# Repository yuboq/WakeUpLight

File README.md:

Currently, this device turns on LED strip at 5AM, and gradually increases in brightness in a half hour period.
Demo can be found here:
https://youtu.be/3JCAbMRWAIY

Eventually, the goal for this project is to create a beautiful standalone alarm clock that can help others wake up more naturally, similar to the Philips Wake Up Light, but with more customizations

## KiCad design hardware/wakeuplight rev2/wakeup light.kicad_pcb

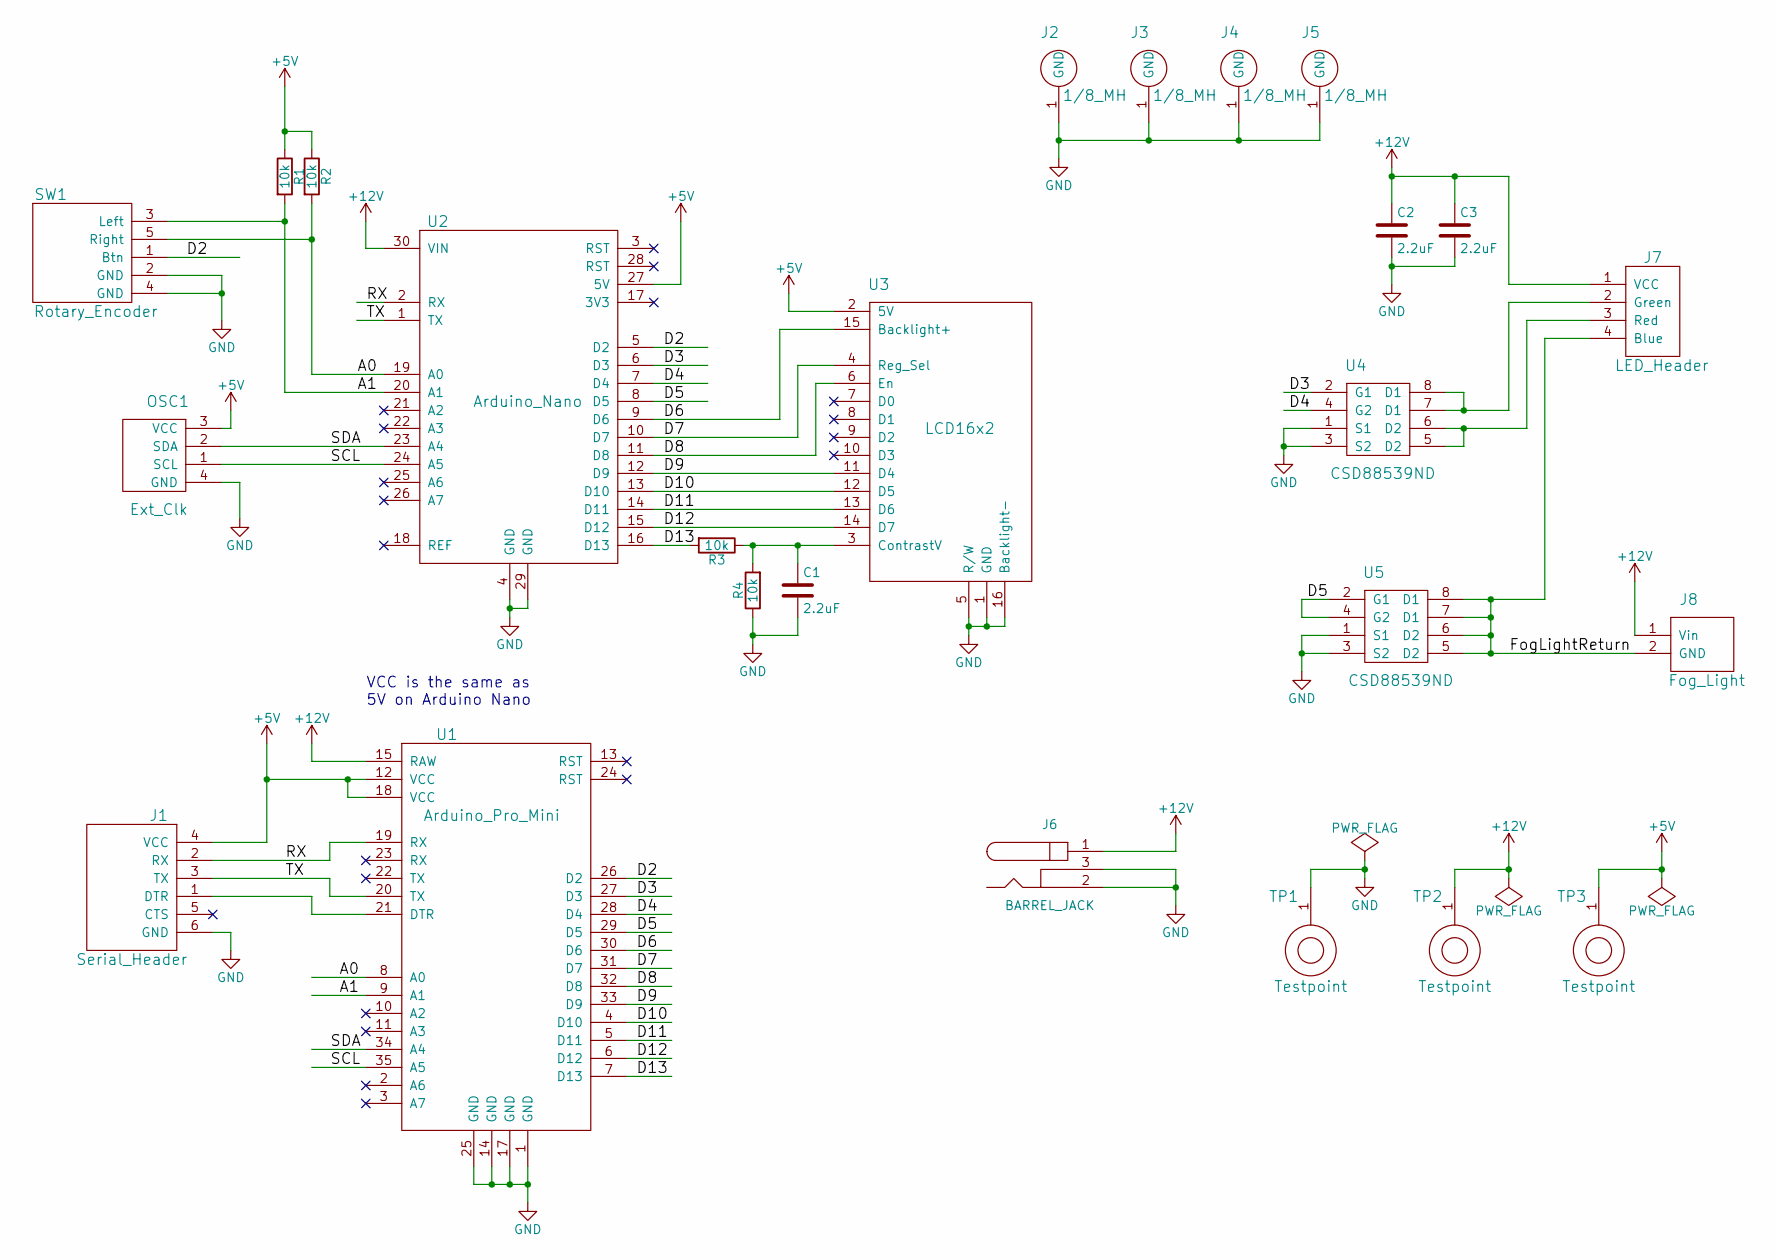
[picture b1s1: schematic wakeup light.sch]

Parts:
C1, C2, C3: 2.2uF; C_0603_HandSoldering
J1: Serial_Header; Pin_Header_Straight_1x06
J2, J3, J4, J5: 1/8_MH; 2.5mm_MH
J6: BARREL_JACK
J7: LED_Header; Pin_Header_Straight_1x04
J8: Fog_Light
OSC1: Ext_Clk; External_Clock
R1, R2, R3, R4: 10k; R_0603_HandSoldering
SW1: Rotary_Encoder; Push_Button
TP1, TP2, TP3: Testpoint
U1: Arduino_Pro_Mini
U2: Arduino_Nano
U3: LCD16x2; LCD_16x2
U4, U5: CSD88539ND; SOIC-8-N

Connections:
+5V: J1.4 (VCC), OSC1.3 (VCC), R1.1, R2.1, TP3.1, U1.12 (VCC), U1.18 (VCC), U2.27 (5V), U3.2 (5V)
+12V: C2.1, C3.1, J6.1, J7.1 (VCC), J8.1 (Vin), TP2.1, U1.15 (RAW), U2.30 (VIN)
/A0: R2.2, SW1.5 (Right), U1.8 (A0), U2.19 (A0)
/A1: R1.2, SW1.3 (Left), U1.9 (A1), U2.20 (A1)
/D2: SW1.1 (Btn), U1.26 (D2), U2.5 (D2)
/D3: U1.27 (D3), U2.6 (D3), U4.2 (G1)
/D4: U1.28 (D4), U2.7 (D4), U4.4 (G2)
/D5: U1.29 (D5), U2.8 (D5), U5.2 (G1), U5.4 (G2)
/D6: U1.30 (D6), U2.9 (D6), U3.15 (Backlight+)
/D7: U1.31 (D7), U2.10 (D7), U3.4 (Reg_Sel)
/D8: U1.32 (D8), U2.11 (D8), U3.6 (En)
/D9: U1.33 (D9), U2.12 (D9), U3.11 (D4)
/D10: U1.4 (D10), U2.13 (D10), U3.12 (D5)
/D11: U1.5 (D11), U2.14 (D11), U3.13 (D6)
/D12: U1.6 (D12), U2.15 (D12), U3.14 (D7)
/D13: R3.2, U1.7 (D13), U2.16 (D13)
/FogLightReturn: J7.4 (Blue), J8.2 (GND), U5.5 (D2), U5.6 (D2), U5.7 (D1), U5.8 (D1)
/RX: J1.2 (RX), U1.19 (RX), U2.2 (RX)
/SCL: OSC1.1 (SCL), U1.35 (A5), U2.24 (A5)
/SDA: OSC1.2 (SDA), U1.34 (A4), U2.23 (A4)
/TX: J1.3 (TX), U1.20 (TX), U2.1 (TX)
GND: C1.2, C2.2, C3.2, J1.6 (GND), J2.1, J3.1, J4.1, J5.1, J6.2, J6.3, OSC1.4 (GND), R4.1, SW1.2 (GND), SW1.4 (GND), TP1.1, U1.1 (GND), U1.14 (GND), U1.17 (GND), U1.25 (GND), U2.4 (GND), U2.29 (GND), U3.1 (GND), U3.5 (R/W), U3.16 (Backlight-), U4.1 (S1), U4.3 (S2), U5.1 (S1), U5.3 (S2)
unnamed: C1.1, R3.1, R4.2, U3.3 (ContrastV)
unnamed: J1.1 (DTR), U1.21 (DTR)
unnamed: J7.2 (Green), U4.7 (D1), U4.8 (D1)
unnamed: J7.3 (Red), U4.5 (D2), U4.6 (D2)

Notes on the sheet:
VCC is the same as 5V on Arduino Nano

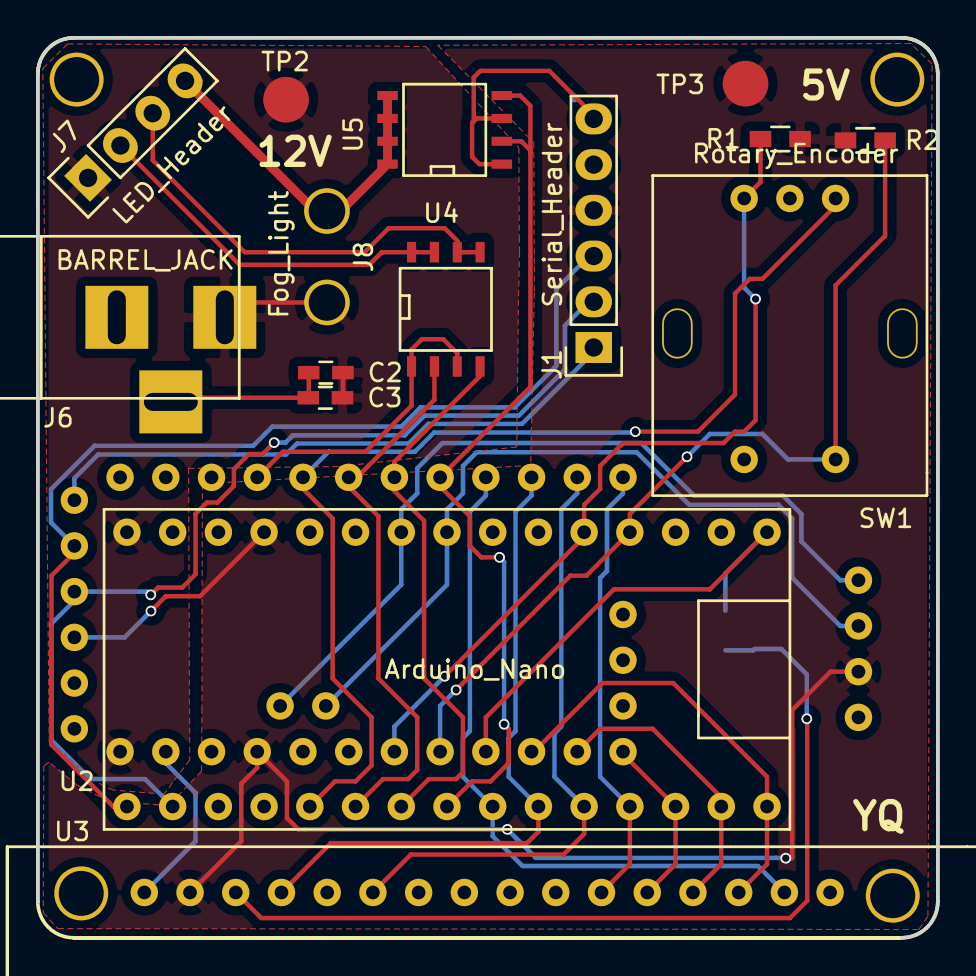
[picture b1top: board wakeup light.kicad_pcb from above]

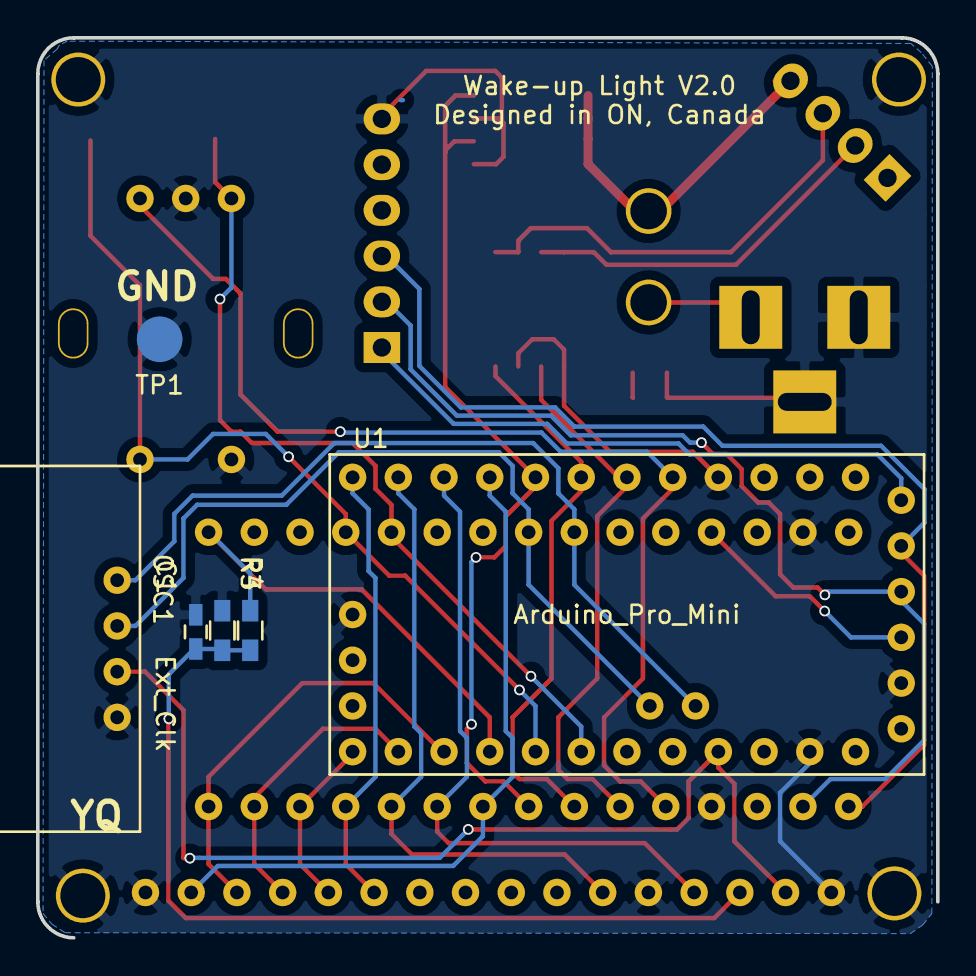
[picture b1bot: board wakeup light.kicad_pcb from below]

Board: 2 copper layers, 50.0 x 50.0 mm, 25 parts (6 on the bottom side), 26 nets.

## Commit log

2015-09-28 added function for external DS3231 clock
2015-09-29 broke the light, but communicating with DS3231
2015-09-29 deleted 'wakeuplight.ino' becuase it was linking c files. Created a single .ino called wakelight to resolve problem. LOL so bad. TODO: modulize the functions in waklight. At least it's reading and tu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
2015-09-29 updated todo list
2015-10-16 changed wakeup time to 6:15am. commmented out serial print statements
2016-01-14 Updated spec documents and reorganized stuff
    Updated todo list
    reorganized specification document
    Reorganized folders for more logical placement
2016-01-14 moved DS3231_set.ino to software folder
2016-01-18 Added custom symbols for wake-up light
    Added symbols for:
    arduino mini, arduino nano, external clock, serial header, LED header,
    16x2 LCD. Updated TODO list
2016-01-19 Added more custom symbols
    Added custom symbols for: FETs, Foglights, pushbutton
    cleaned up arduino symbols by grouping GPIO pins, power pins, gnd, etc
2016-01-21 Started schematics
    Completed wiring for 16x2 LCD with Arduino Mini
    Completed Arduino mini wiring
    Fixed up some symbols so pins are grouped more logically
2016-01-22 updated schematic with a few more wires
    connected a few more wires to components, modified the serial header to
    fit nicer in schematic
2016-01-23 Completed rough schematic
    Everything should be there.
2016-01-26 Added footprints for all parts
2016-01-28 DRC on schematic is complete
    Modified pins on symbols to appropriate electrical type (input, output,
    bidirectional, etc)
    Annotated schematics
    Resolved all DRC errors.
2016-01-29 updated netlist and linked components to footprints
2016-01-31 components placed
    Schematics updated with mounting holes
    components placed, need to wire them up
2016-01-31 Completed layout
    Wiring complete
    Need to double check and send off to manufacture.
2016-02-01 Boards ordered!
    gerbers generated and are on the way.
2016-02-08 Tests rotary encoder functionality in sandbox
2016-02-09 Link youtube demo
2016-02-22 includes PDF schematics
    For easier reading!
    includes component values
2016-04-08 uses correct pins for PCB version of wakeup light
    wake-up light on the custom PCB uses different pins compared to
    breadboard version. Updates the pins to match those on schematics (for
    custom PCB)
2016-04-10 update GPIO pins to reflect those used in schematics
    List required mods for first build of the board
    Add notes about improvements for next revision
2016-04-16 modify arduino GPIOs to match those on the schematics
2016-04-19 Initial commit for V2.0 HW
    HW completed
    Layout completed
    Tasks updated
